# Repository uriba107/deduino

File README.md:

# DEDUino
Arduino Based DED for Falcon BMS.
Project Blog: http://pit.uriba.org

## Requirements:
### Hardware:
1. an Arduino or compatible board:
  * Arduino Uno (or compatible)
  * Arduino Micro (or compatible)
  * Arduino Due (or compatible)
  * all similar Arduino/Arduino-like variations (Mega/leonardo/pro Micro) will require code to be adjusted
2. For DED/PFL: One 2.8" or 3.2" 256*64 OLED display (yellow or green), SSD1322 based
  * [BuyDisplay 2.8" yellow on black oled](http://www.buydisplay.com/default/spi-2-8-inch-oled-arduino-256x64-graphic-module-with-pcb-yellow-on-black)
  * [BuyDisplay 3.2" green on black oled](http://www.buydisplay.com/default/spi-oled-manufacturer-256x64-display-panel-supplier-green-on-black)
  * other screens may be also compatible (as long as they are SSD1322 based) - but may require different wiring.
3. For FFI: one 1.3" 128*64 OLED white on black. SSD1306 or SH1106 based
  * [Adafruit 1.3" 128*64 OLED](http://www.adafruit.com/product/938)
  * Generic 1.3" OLED (off the internet), will do fine as long as it's of one of the supported chipsets.
  * Other displays might be also compatible - but may require code edit
4. For Indexers/Caution panel:
  * [PCF8574 8-bit I2C I/O Expander](http://www.ebay.com/sch/sis.html?_nkw=PCF8574P+PCF8574+DIP-16+NXP%2FPHI+Remote+8-bit+I%2FO+Expander+IC) - for Indexers
  * [MCP23017 16-bit I2C I/O Expander](http://www.ebay.com/sch/sis.html?_nkw=MCP23017-E%2FSP+DIP28+16-Bit+I%2FO+Expander+with+I2C+Interface+IC) - optional 16 bit extender (useful for caution panel and other things)
  * LEDs of your choosing (If using attached PCB design unmodified - 5mm pirahna leds are used)
  * Resistors (220-330 ohm reesistors would be a good place to start)
  * Legacy SPI lights are using [74HC595 Shift Register](http://www.adafruit.com/product/450) - you can find them on ebay as well.

### Software:
1. Arduino IDE
2. Windows Vista and up with .net 4.5 installed (XP does not support .net4.5 and I've not tested the supplied connector app with .net4.0)
3. Falcon BMS 4.32+

## How to use:
### Initial setup:
1. Download and install the Arduino IDE (if not already installed)
2. Download the Arduino code
3. In the Arduino IDE - "Add library" choose "U8g2_16bit" it's standard U8g2 2.12.6 with 16BIT support enabled (required for the large displays)
4. In "config.h" and uncomment the correct define for your arduino version (Uno, Micro or Due).
5. In "config.h" Uncomment the define statements for the periferials you want to use. please note that adding both DED and PFL may have an impact on performace.
6. Wire prereferials according the the pinout in the code. Please pay attention to the SCK and MOSI pins and the latchpins
7. Upload code to your Arduino.
8. Download the DEDuino Windows app and place it in a folder of your choosing (no installation required)

### running the project:
1. launch DEDuino App
2. Select proper COM port for the arduino to be used and hit "Start"
3. Once connected - Windows app will indicate connected status and all displays and leds should be blanked except for FFI screen that will show "00000".
4. Launch Falcon BMS - As soon as you enter the cockpit, all the instruments connected should display acording to the pit.

## Supported instruments:
1. Displays:
  * DED - Tier 1
  * FFI - Tier 1
  * PFD - Tier 1 (disabled by default due to performance considuration)
2. Lights:
  * Indexers - Tier 1
  * Caution Panel - Tier 1 (Disabled by default due to performance consideration)
3. Future supported instruments:
  * Glareshield lighs - TBD
  * Threat Warning Prime - TBD
  * CMDS - via OLED screen, TBD

## Knows issues:
1. Activating more the one large res display (DED/PFD) will cause performace degradation. Activating more then two might cause noticable lag without further optimization to Arduino code (not yet implemented).
2. "lamp test" might not work properly for Caution panel is some scenarios.
3. When using SPI for driving multiple light arrays, there are issues including freezes, wrongly timed blinks and all sort of wierd shananigans. That is way, I2C is now the primary, prefered protocol for driving lights. SPI support will not be extended, and only retained for comptability.

## PCB
In the PCB folder you would find Eagle files and PDFs with schematics and board drawings. These are the boards I'm working with. You can make them yourself by hand soldering the connectors (see schematics) or source them out to production. All boards were edited using the Free version of Eagle (version 7).

## Enclosures
In the "enclosure" folders you'll find some stractual stuff, like the foamboard DED box.

## Notes and remarks
While the project is OpenSource. Currently I'm holding back the source code for the PC connector application. That is done because The code is a mess, I need to properly document it before I release it. Hopfully sometime this year. Nothing secret about it, promise :)
Big Thanks to Oliver Kraus (olikraus) who wrote [u8glib](https://github.com/olikraus/u8glib)/[u8g2](https://github.com/olikraus/u8g2) without him, none of this would have been possible.

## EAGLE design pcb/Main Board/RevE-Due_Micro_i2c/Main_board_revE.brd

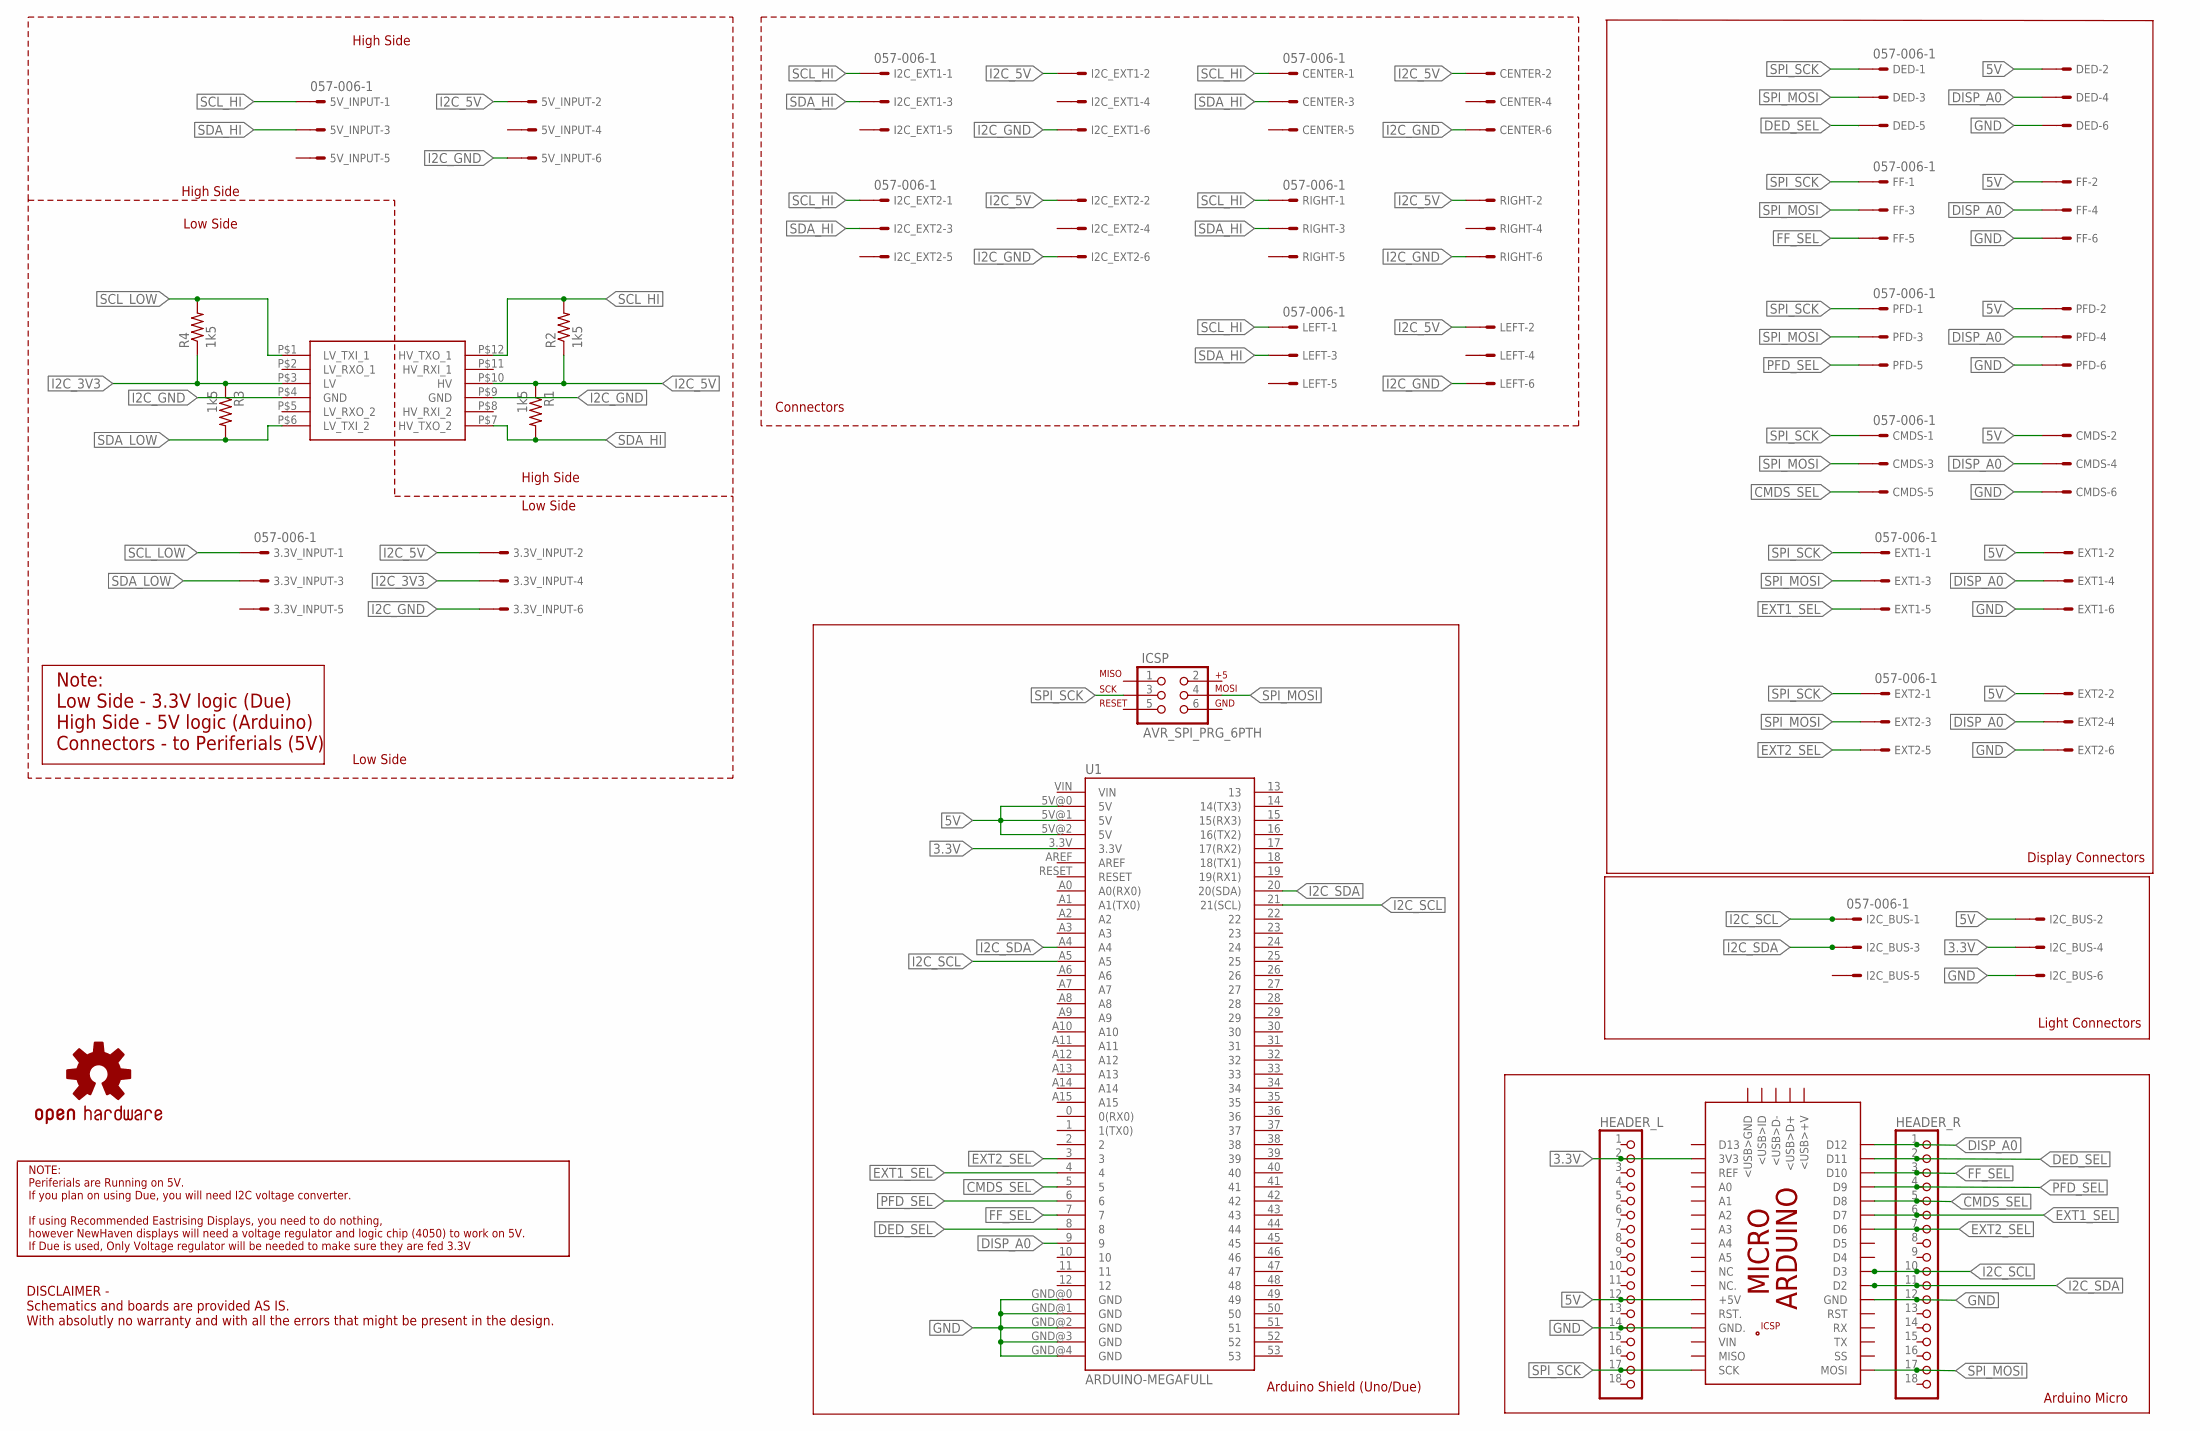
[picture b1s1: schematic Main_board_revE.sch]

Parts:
3.3V_INPUT, 5V_INPUT: 057-006-1
CENTER: 057-006-1
CMDS: 057-006-1
DED: 057-006-1
EXT1, EXT2: 057-006-1
FF: 057-006-1
HEADER_L: PINHD-1X18; 1X18
HEADER_R: PINHD-1X18; 1X18
I2C_BUS, I2C_EXT1, I2C_EXT2: 057-006-1
ICSP: AVR_SPI_PRG_6PTH; 2X3
LEFT: 057-006-1
LOGO1: OSHW-LOGOM; OSHW-LOGO-M
PFD: 057-006-1
R1, R2, R3, R4: 1k5; 0805
RIGHT: 057-006-1
U1: ARDUINO-MEGAFULL; ARDUINO_MEGA
U$1: LOGIC_LEVEL_CONVERTER

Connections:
3.3V: HEADER_L.2, I2C_BUS.4, U1.3.3V
5V: CMDS.2, DED.2, EXT1.2, EXT2.2, FF.2, HEADER_L.12, I2C_BUS.2, PFD.2, U1.5V@0 (5V), U1.5V@1 (5V), U1.5V@2 (5V)
CMDS_SEL: CMDS.5, HEADER_R.5, U1.5
DED_SEL: DED.5, HEADER_R.2, U1.8
DISP_A0: CMDS.4, DED.4, EXT1.4, EXT2.4, FF.4, HEADER_R.1, PFD.4, U1.9
EXT1_SEL: EXT1.5, HEADER_R.6, U1.4
EXT2_SEL: EXT2.5, HEADER_R.7, U1.3
FF_SEL: FF.5, HEADER_R.3, U1.7
GND: CMDS.6, DED.6, EXT1.6, EXT2.6, FF.6, HEADER_L.14, HEADER_R.12, I2C_BUS.6, PFD.6, U1.GND@0 (GND), U1.GND@1 (GND), U1.GND@2 (GND), U1.GND@3 (GND), U1.GND@4 (GND)
I2C_3V3: 3.3V_INPUT.4, R3.1, R4.1, U$1.P$3 (LV)
I2C_5V: 3.3V_INPUT.2, 5V_INPUT.2, CENTER.2, I2C_EXT1.2, I2C_EXT2.2, LEFT.2, R1.1, R2.1, RIGHT.2, U$1.P$10 (HV)
I2C_GND: 3.3V_INPUT.6, 5V_INPUT.6, CENTER.6, I2C_EXT1.6, I2C_EXT2.6, LEFT.6, RIGHT.6, U$1.P$4 (GND), U$1.P$9 (GND)
I2C_SCL: HEADER_R.10, I2C_BUS.1, U1.21 (21(SCL)), U1.A5
I2C_SDA: HEADER_R.11, I2C_BUS.3, U1.20 (20(SDA)), U1.A4
PFD_SEL: HEADER_R.4, PFD.5, U1.6
SCL_HI: 5V_INPUT.1, CENTER.1, I2C_EXT1.1, I2C_EXT2.1, LEFT.1, R2.2, RIGHT.1, U$1.P$12 (HV_TXO_1)
SCL_LOW: 3.3V_INPUT.1, R4.2, U$1.P$1 (LV_TXI_1)
SDA_HI: 5V_INPUT.3, CENTER.3, I2C_EXT1.3, I2C_EXT2.3, LEFT.3, R1.2, RIGHT.3, U$1.P$7 (HV_TXO_2)
SDA_LOW: 3.3V_INPUT.3, R3.2, U$1.P$6 (LV_TXI_2)
SPI_MOSI: CMDS.3, DED.3, EXT1.3, EXT2.3, FF.3, HEADER_R.17, ICSP.4, PFD.3
SPI_SCK: CMDS.1, DED.1, EXT1.1, EXT2.1, FF.1, HEADER_L.17, ICSP.3, PFD.1

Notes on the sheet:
Arduino Shield (Uno/Due)
Arduino Micro
Light Connectors
Display Connectors
DISCLAIMER - Schematics and boards are provided AS IS. With absolutly no warranty and with all the errors that might be present in the design.
NOTE: Periferials are Running on 5V. If you plan on using Due, you will need I2C voltage converter. If using Recommended Eastrising Displays, you need to do nothing, however NewHaven displays will need a voltage regulator and logic chip (4050) to work on 5V. If Due is used, Only Voltage regulator w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
Low Side
High Side
Connectors
Note: Low Side - 3.3V logic (Due) High Side - 5V logic (Arduino) Connectors - to Periferials (5V)

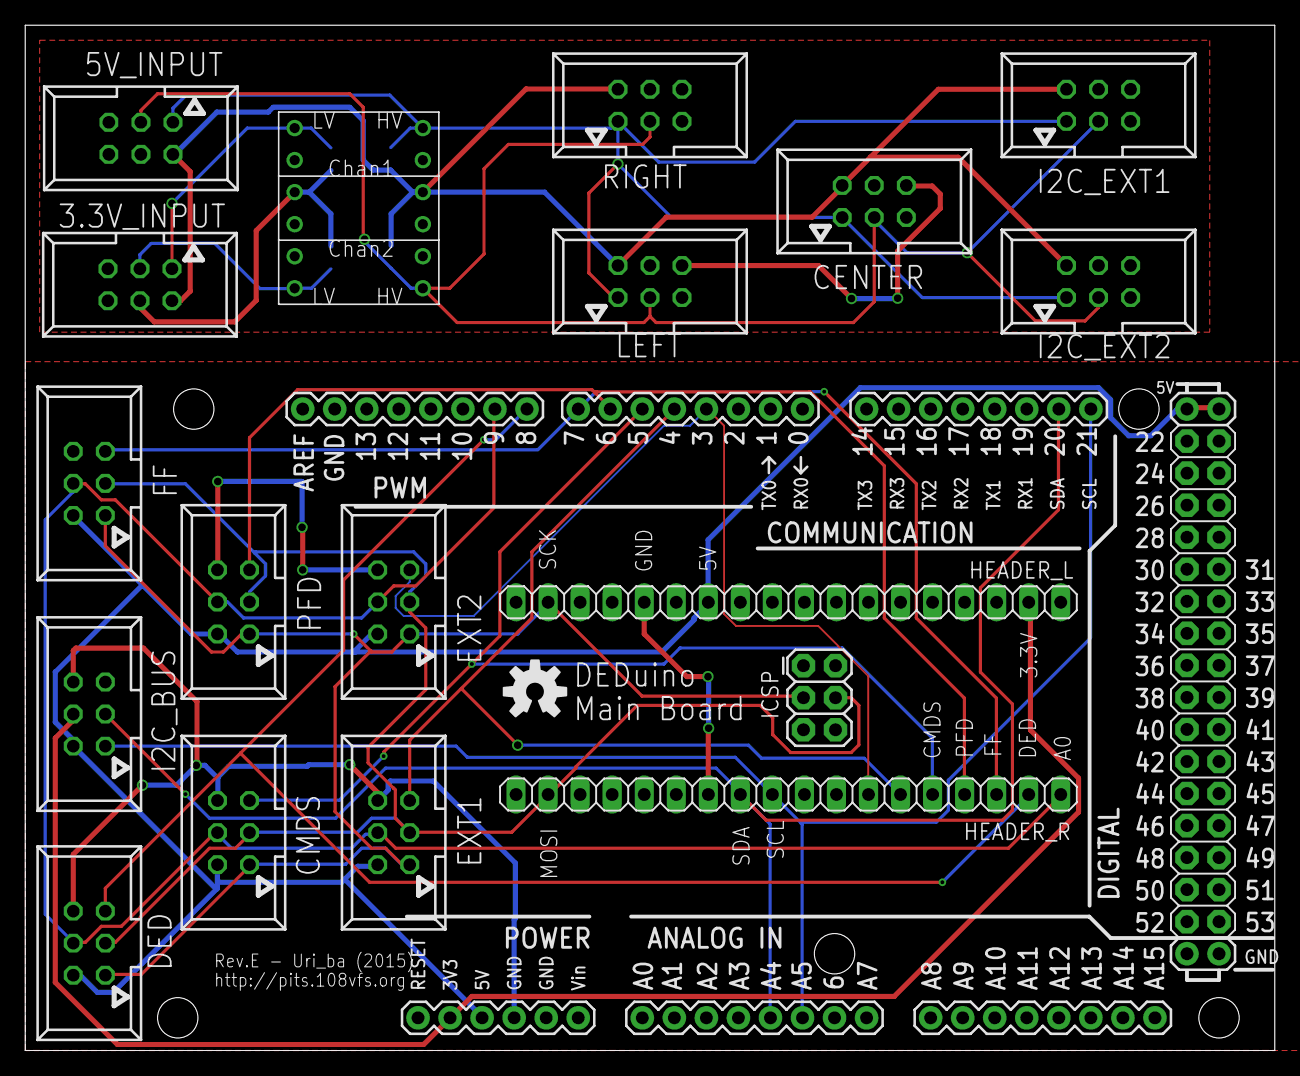
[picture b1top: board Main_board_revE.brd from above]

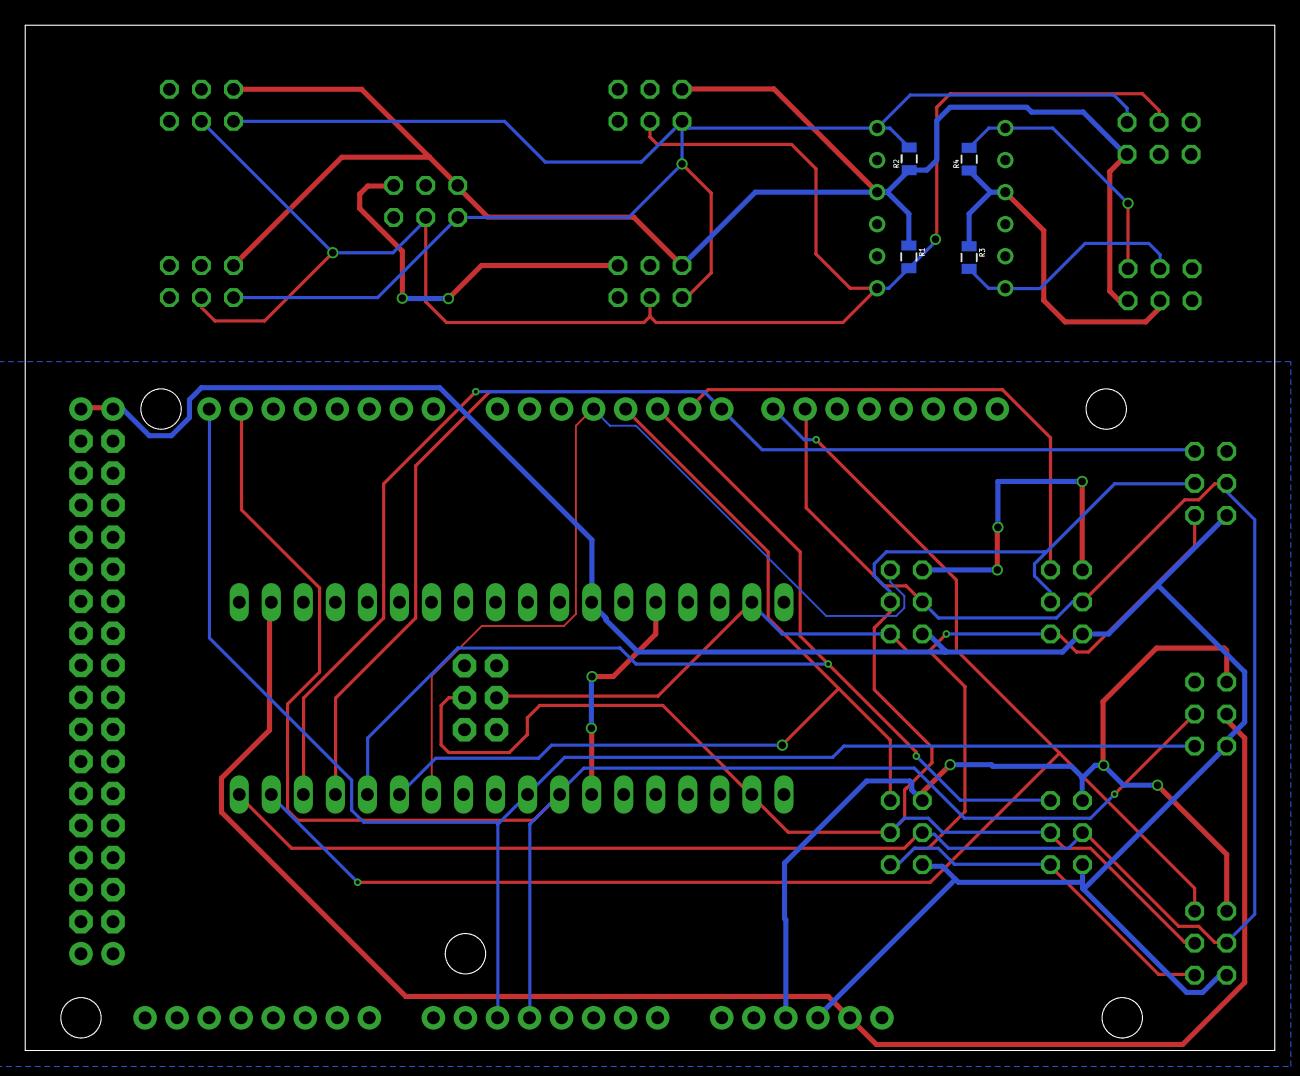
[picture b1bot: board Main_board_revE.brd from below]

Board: 2 copper layers, 99.1 x 81.3 mm, 24 parts (4 on the bottom side), 21 nets.

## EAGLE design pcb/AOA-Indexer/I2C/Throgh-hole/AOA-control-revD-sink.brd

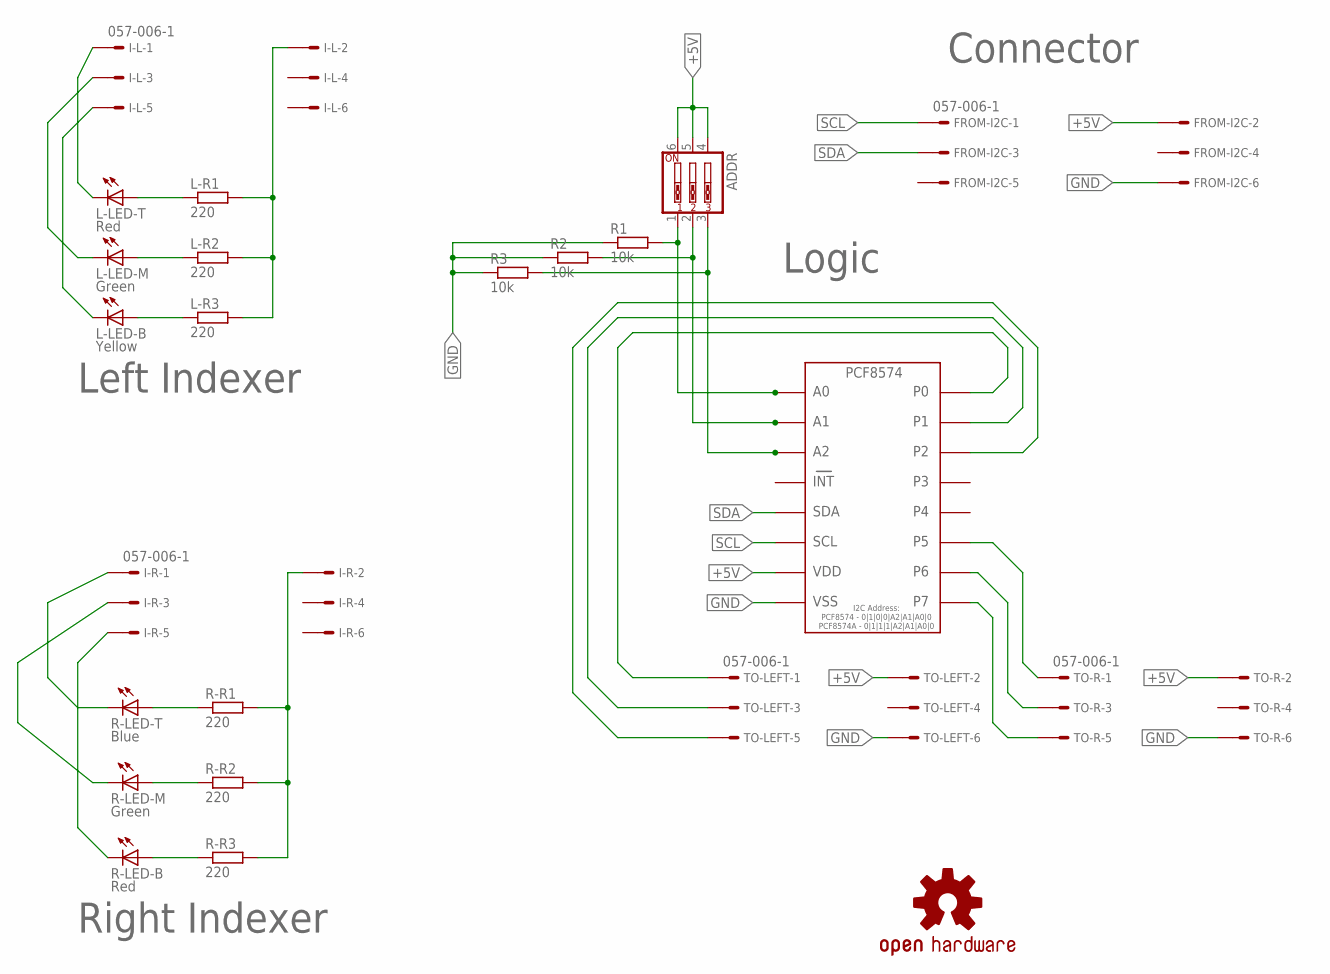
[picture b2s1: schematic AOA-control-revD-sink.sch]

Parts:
ADDR: SW_DIP-3; EDG-03
FROM-I2C: 057-006-1
I-L: 057-006-1
I-R: 057-006-1
L-LED-B: Yellow; CP41B
L-LED-M: Green; CP41B
L-LED-T: Red; CP41B
L-R1, L-R2, L-R3: 220; 0204/7
LOGO1: OSHW-LOGOS; OSHW-LOGO-S
R1, R2, R3: 10k; 0204/7
R-LED-B: Red; CP41B
R-LED-M: Green; CP41B
R-LED-T: Blue; CP41B
R-R1, R-R2, R-R3: 220; 0204/7
TO-LEFT: 057-006-1
TO-R: 057-006-1
U$1: PCF8574P/AP; DIP16

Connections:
5V-L: I-L.2, L-R1.2, L-R2.2, L-R3.2
5V-R: I-R.2, R-R1.2, R-R2.2, R-R3.2
+5V: ADDR.4, ADDR.5, ADDR.6, FROM-I2C.2, TO-LEFT.2, TO-R.2, U$1.VDD
A0: ADDR.1, R1.2, U$1.A0
A1: ADDR.2, R2.2, U$1.A1
A2: ADDR.3, R3.2, U$1.A2
GND: FROM-I2C.6, R1.1, R2.1, R3.1, TO-LEFT.6, TO-R.6, U$1.VSS
unnamed: I-L.1, L-LED-T.1 (C), L-LED-T.4 (C)
unnamed: I-L.3, L-LED-M.1 (C), L-LED-M.4 (C)
unnamed: I-L.5, L-LED-B.1 (C), L-LED-B.4 (C)
unnamed: R-LED-B.2 (A), R-LED-B.3 (A), R-R3.1
unnamed: I-R.1, R-LED-T.1 (C), R-LED-T.4 (C)
unnamed: I-R.3, R-LED-M.1 (C), R-LED-M.4 (C)
unnamed: I-R.5, R-LED-B.1 (C), R-LED-B.4 (C)
unnamed: R-LED-M.2 (A), R-LED-M.3 (A), R-R2.1
unnamed: R-LED-T.2 (A), R-LED-T.3 (A), R-R1.1
unnamed: L-LED-T.2 (A), L-LED-T.3 (A), L-R1.1
unnamed: TO-LEFT.1, U$1.P0
unnamed: L-LED-M.2 (A), L-LED-M.3 (A), L-R2.1
unnamed: L-LED-B.2 (A), L-LED-B.3 (A), L-R3.1
unnamed: TO-LEFT.3, U$1.P1
unnamed: TO-LEFT.5, U$1.P2
unnamed: TO-R.1, U$1.P5
unnamed: TO-R.3, U$1.P6
unnamed: TO-R.5, U$1.P7
SCL: FROM-I2C.1, U$1.SCL
SDA: FROM-I2C.3, U$1.SDA

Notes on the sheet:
Connector
Logic
Left Indexer
Right Indexer

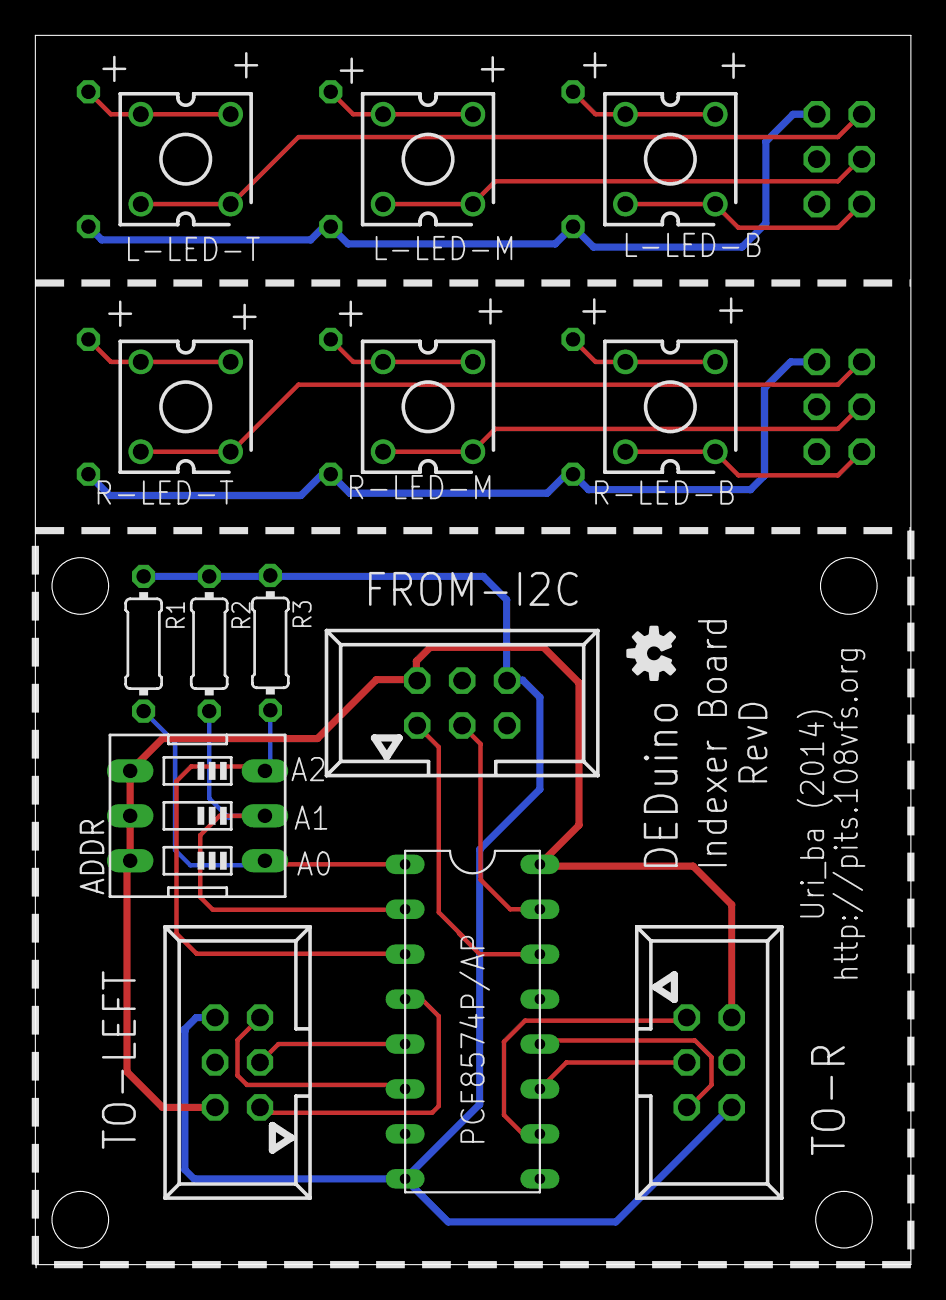
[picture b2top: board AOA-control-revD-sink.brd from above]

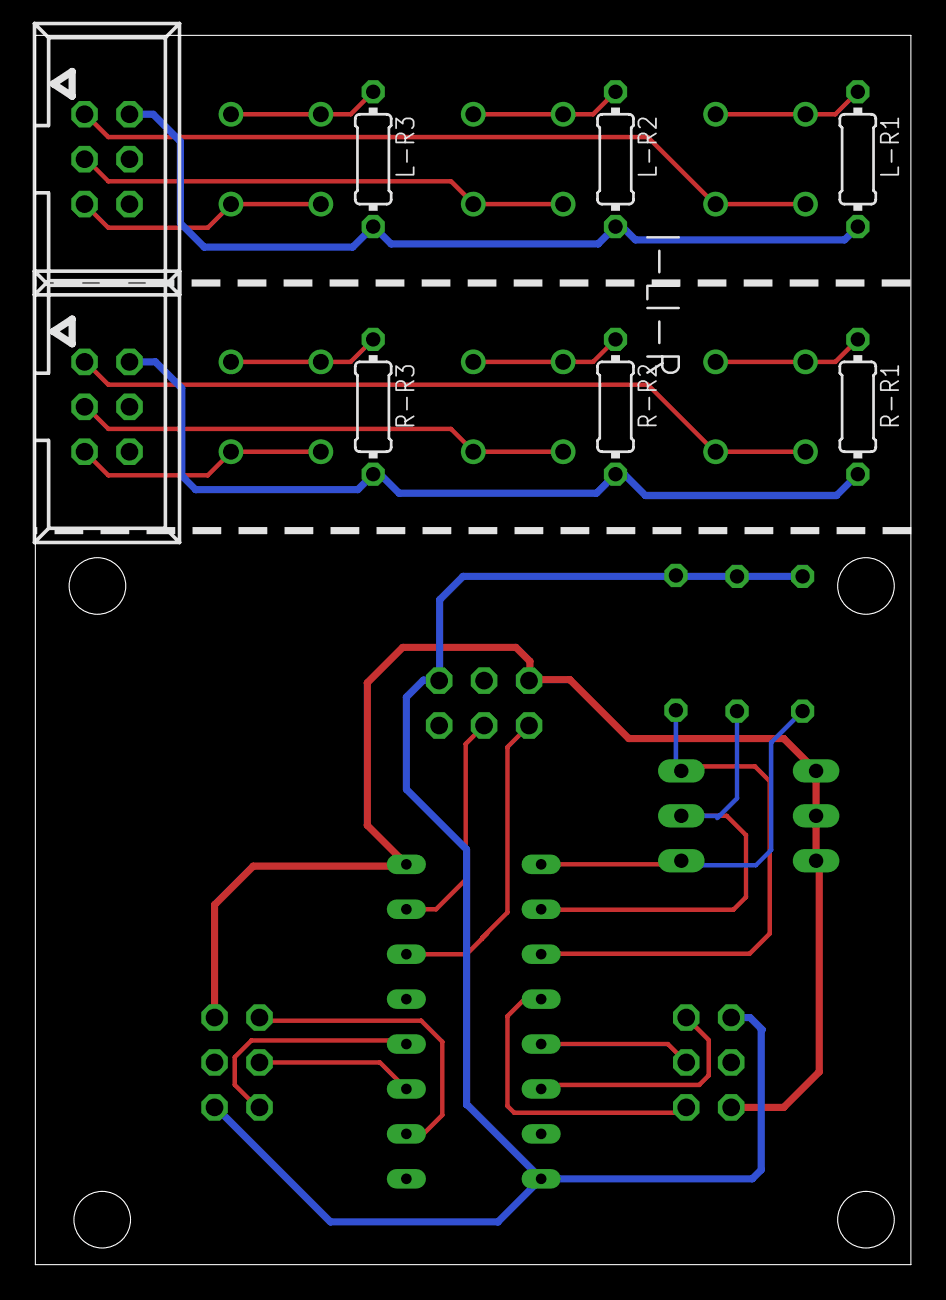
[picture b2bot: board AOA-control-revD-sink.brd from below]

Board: 2 copper layers, 49.5 x 69.5 mm, 23 parts (8 on the bottom side), 27 nets.

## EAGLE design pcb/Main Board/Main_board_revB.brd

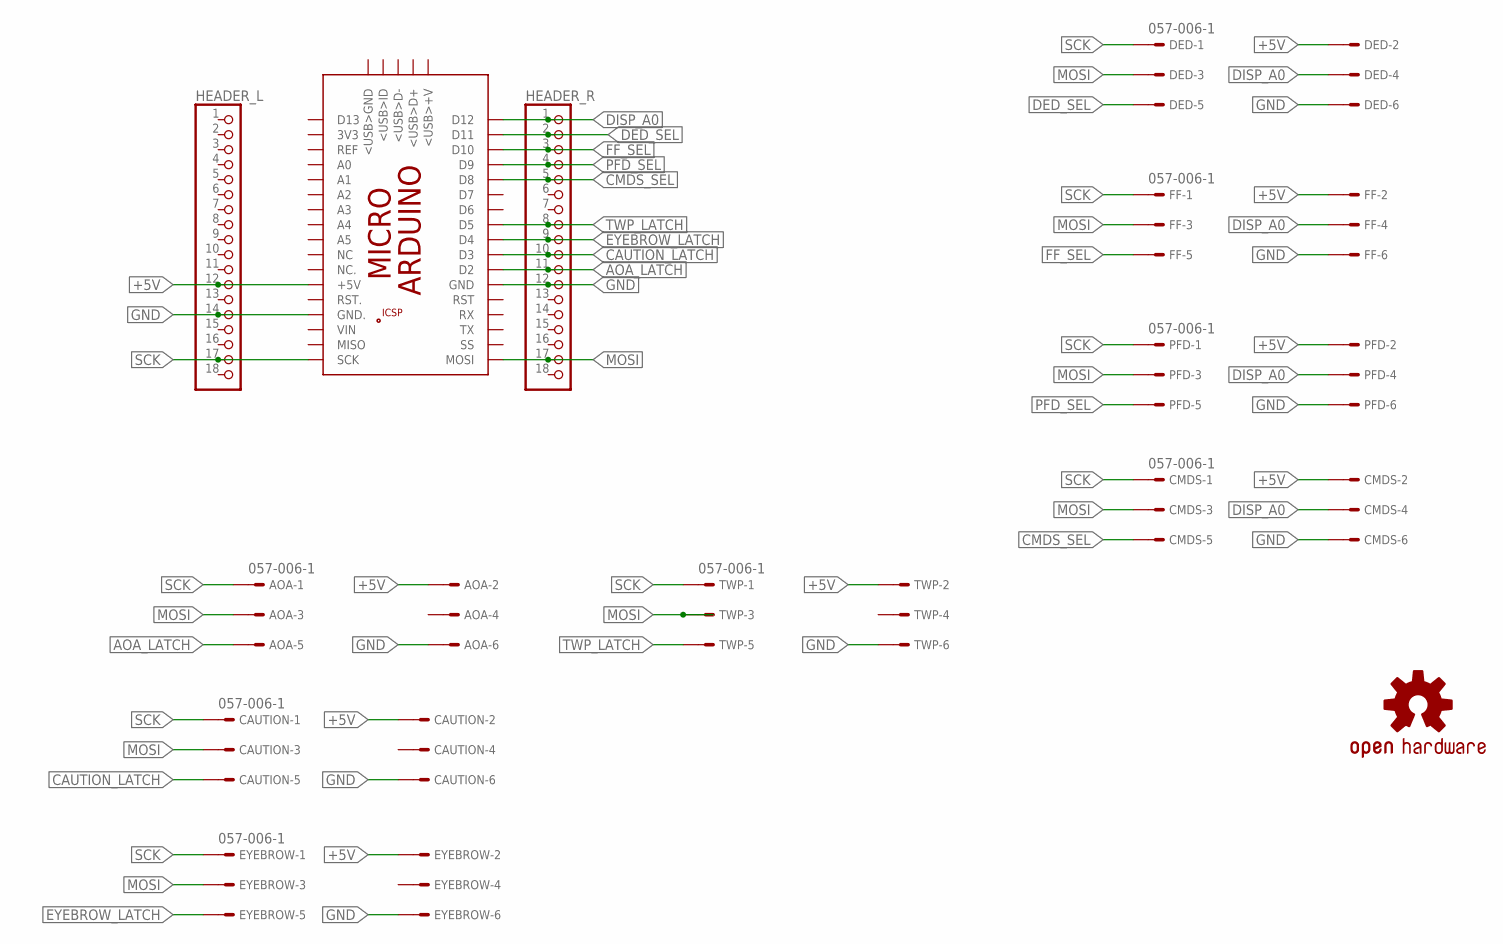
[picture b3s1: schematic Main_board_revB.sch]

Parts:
AOA: 057-006-1
CAUTION: 057-006-1
CMDS: 057-006-1
DED: 057-006-1
EYEBROW: 057-006-1
FF: 057-006-1
HEADER_L: PINHD-1X18; 1X18
HEADER_R: PINHD-1X18; 1X18
LOGO1: OSHW-LOGOL; OSHW-LOGO-L
PFD: 057-006-1
TWP: 057-006-1

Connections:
+5V: AOA.2, CAUTION.2, CMDS.2, DED.2, EYEBROW.2, FF.2, HEADER_L.12, PFD.2, TWP.2
AOA_LATCH: AOA.5, HEADER_R.11
CAUTION_LATCH: CAUTION.5, HEADER_R.10
CMDS_SEL: CMDS.5, HEADER_R.5
DED_SEL: DED.5, HEADER_R.2
DISP_A0: CMDS.4, DED.4, FF.4, HEADER_R.1, PFD.4
EYEBROW_LATCH: EYEBROW.5, HEADER_R.9
FF_SEL: FF.5, HEADER_R.3
GND: AOA.6, CAUTION.6, CMDS.6, DED.6, EYEBROW.6, FF.6, HEADER_L.14, HEADER_R.12, PFD.6, TWP.6
MOSI: AOA.3, CAUTION.3, CMDS.3, DED.3, EYEBROW.3, FF.3, HEADER_R.17, PFD.3, TWP.3
PFD_SEL: HEADER_R.4, PFD.5
SCK: AOA.1, CAUTION.1, CMDS.1, DED.1, EYEBROW.1, FF.1, HEADER_L.17, PFD.1, TWP.1
TWP_LATCH: HEADER_R.8, TWP.5

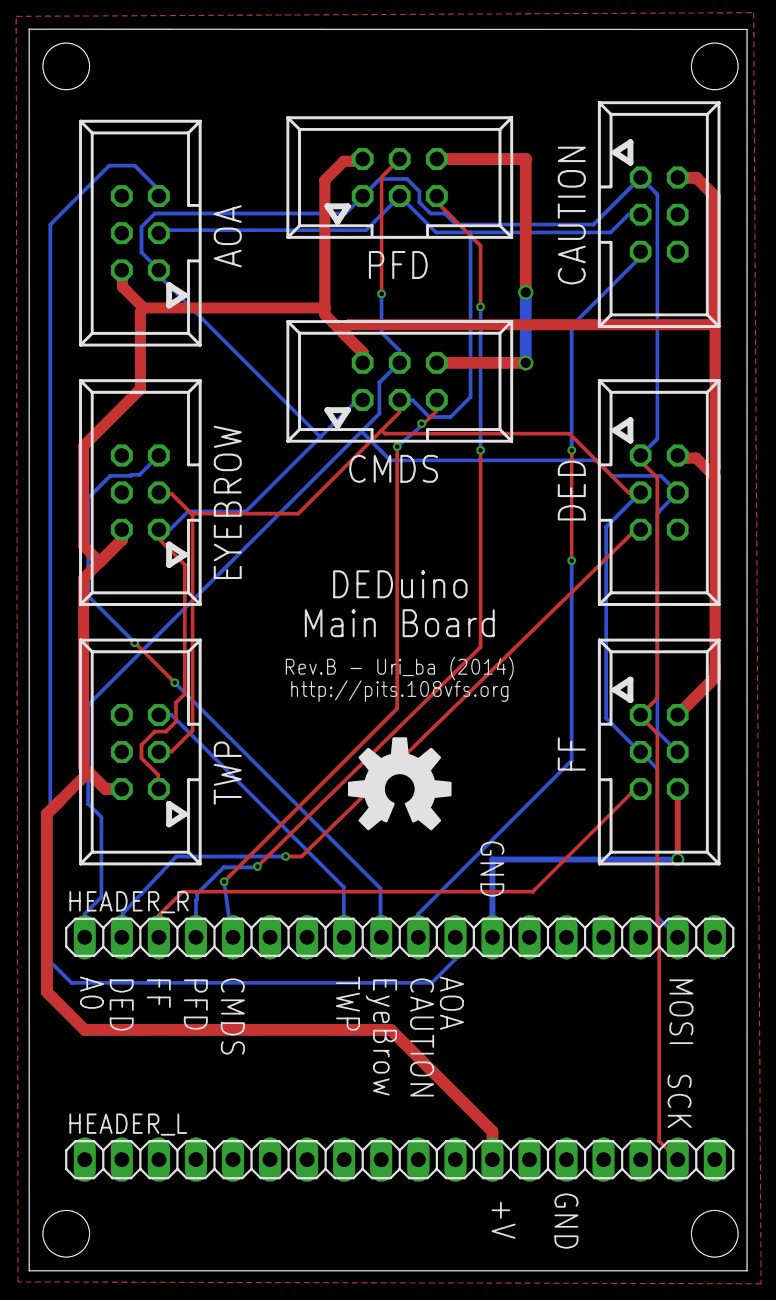
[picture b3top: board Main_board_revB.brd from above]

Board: 2 copper layers, 49.2 x 85.1 mm, 11 parts (0 on the bottom side), 13 nets.

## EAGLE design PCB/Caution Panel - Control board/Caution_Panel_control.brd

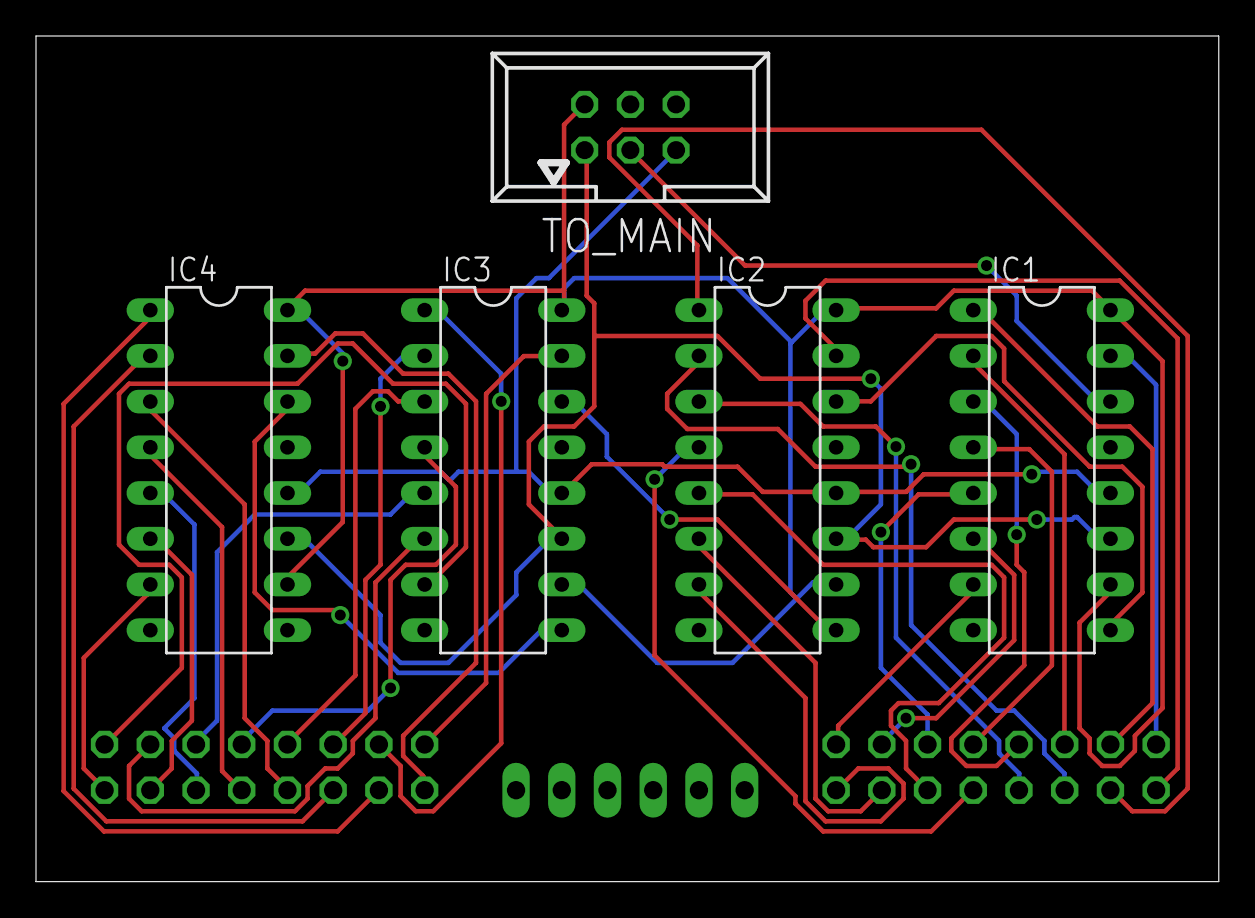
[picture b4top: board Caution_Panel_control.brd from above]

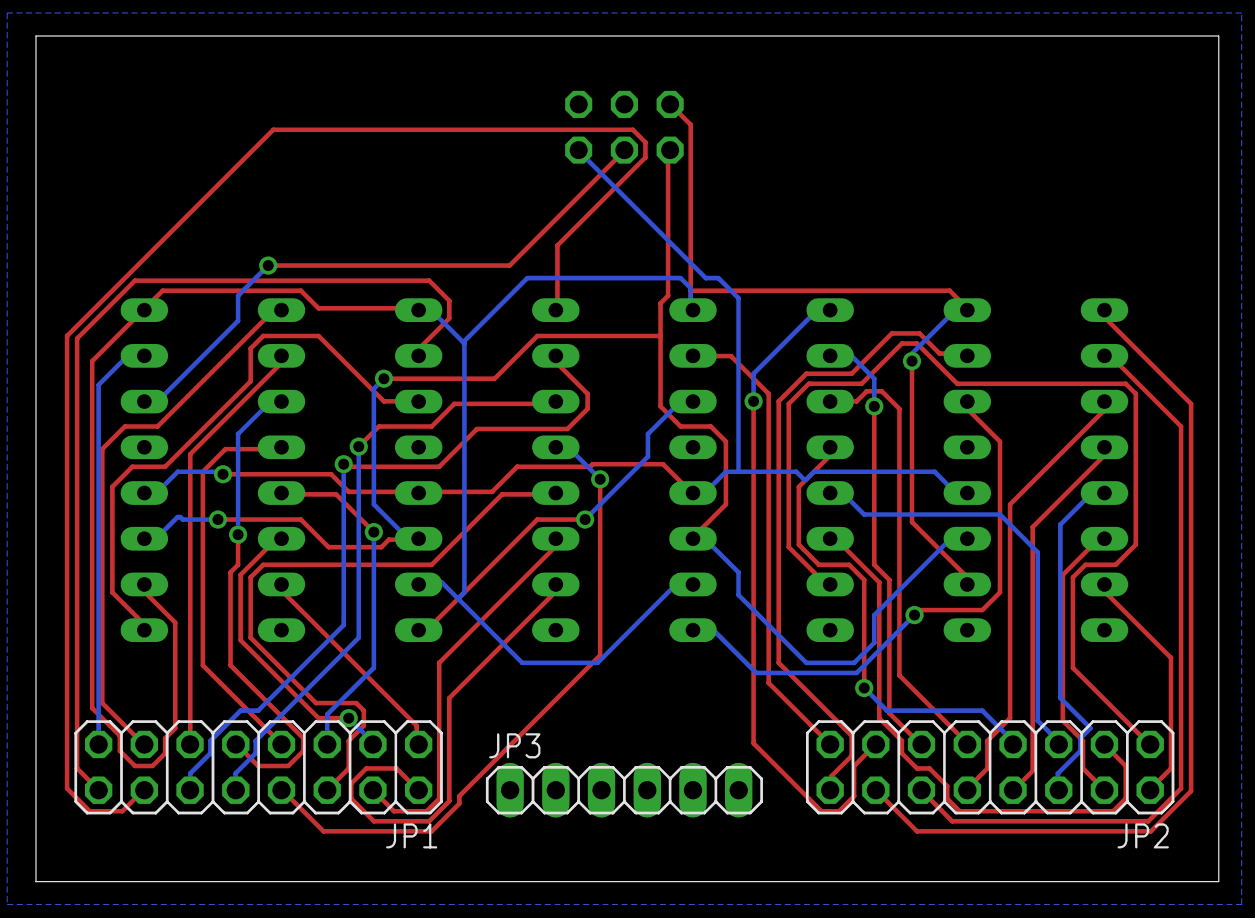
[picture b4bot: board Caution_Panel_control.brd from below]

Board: 2 copper layers, 65.7 x 47.0 mm, 8 parts (3 on the bottom side), 40 nets.

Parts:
IC1, IC2, IC3, IC4: 74HC595N; DIL16
JP1, JP2: 2X08
JP3: 1X06
TO_MAIN: 057-006-1

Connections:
+5V: IC1.10, IC1.16, IC2.10, IC2.16, IC3.10, IC3.16, IC4.10, IC4.16, TO_MAIN.2
CAUTION_LATCH: IC1.12, IC2.12, IC3.12, IC4.12, TO_MAIN.5
DATA_IC2: IC1.9, IC2.14
DATA_IC3: IC2.9, IC3.14
DATA_IC4: IC3.9, IC4.14
GND: IC1.8, IC1.13, IC2.8, IC2.13, IC3.8, IC3.13, IC4.8, IC4.13, JP3.1, JP3.2, JP3.3, JP3.4, JP3.5, JP3.6, TO_MAIN.6
LIGHT_CLK: IC1.11, IC2.11, IC3.11, IC4.11, TO_MAIN.1
LIGHT_DATA: IC1.14, TO_MAIN.3
unnamed: IC1.15, JP1.15
unnamed: IC1.1, JP1.13
unnamed: IC1.2, JP1.11
unnamed: IC1.3, JP1.9
unnamed: IC1.4, JP1.7
unnamed: IC1.5, JP1.5
unnamed: IC1.6, JP1.3
unnamed: IC1.7, JP1.1
unnamed: IC2.15, JP1.16
unnamed: IC2.1, JP1.14
unnamed: IC2.2, JP1.12
unnamed: IC2.3, JP1.10
unnamed: IC2.4, JP1.8
unnamed: IC2.5, JP1.6
unnamed: IC2.6, JP1.4
unnamed: IC2.7, JP1.2
unnamed: IC4.7, JP2.2
unnamed: IC4.6, JP2.4
unnamed: IC4.5, JP2.6
unnamed: IC4.4, JP2.8
unnamed: IC4.3, JP2.10
unnamed: IC4.2, JP2.12
unnamed: IC4.1, JP2.14
unnamed: IC4.15, JP2.16
unnamed: IC3.7, JP2.1
unnamed: IC3.5, JP2.5
unnamed: IC3.6, JP2.3
unnamed: IC3.4, JP2.7
unnamed: IC3.3, JP2.9
unnamed: IC3.2, JP2.11
unnamed: IC3.1, JP2.13
unnamed: IC3.15, JP2.15

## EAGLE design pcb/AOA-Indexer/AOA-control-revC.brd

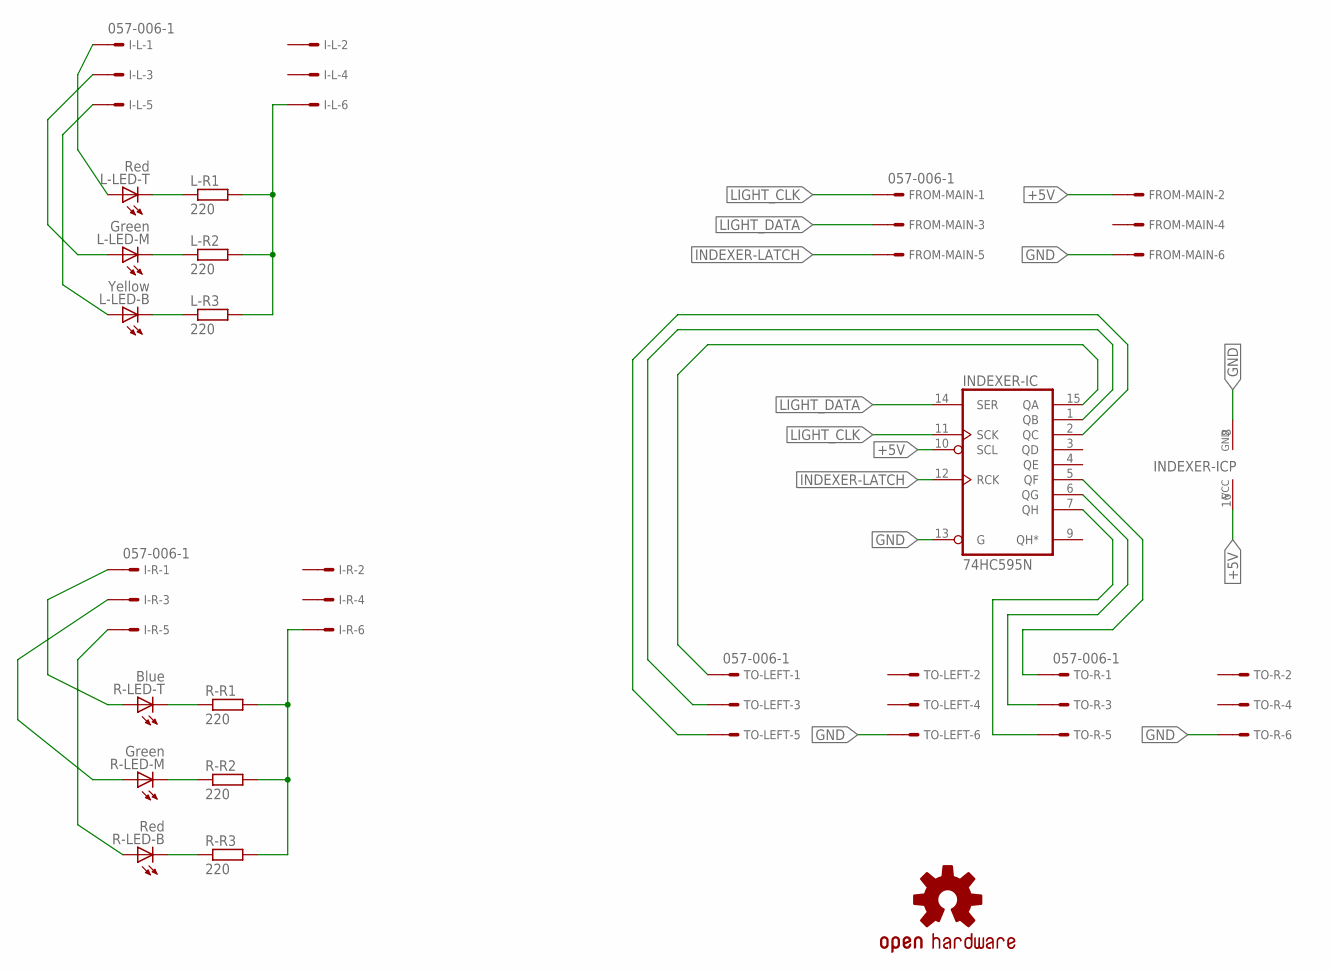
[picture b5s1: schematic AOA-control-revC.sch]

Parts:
FROM-MAIN: 057-006-1
I-L: 057-006-1
I-R: 057-006-1
INDEXER-IC: 74HC595N; DIL16
L-LED-B: Yellow; CP41B
L-LED-M: Green; CP41B
L-LED-T: Red; CP41B
L-R1, L-R2, L-R3: 220; 0204/7
LOGO1: OSHW-LOGOS; OSHW-LOGO-S
R-LED-B: Red; CP41B
R-LED-M: Green; CP41B
R-LED-T: Blue; CP41B
R-R1, R-R2, R-R3: 220; 0204/7
TO-LEFT: 057-006-1
TO-R: 057-006-1

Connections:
+5V: FROM-MAIN.2, INDEXER-IC.10 (SCL), INDEXER-IC.16 (VCC)
GND: FROM-MAIN.6, I-L.6, I-R.6, INDEXER-IC.8 (GND), INDEXER-IC.13 (G), L-R1.2, L-R2.2, L-R3.2, R-R1.2, R-R2.2, R-R3.2, TO-LEFT.6, TO-R.6
INDEXER-LATCH: FROM-MAIN.5, INDEXER-IC.12 (RCK)
L-B: INDEXER-IC.2 (QC), TO-LEFT.5
L-M: INDEXER-IC.1 (QB), TO-LEFT.3
L-T: INDEXER-IC.15 (QA), TO-LEFT.1
LIGHT_CLK: FROM-MAIN.1, INDEXER-IC.11 (SCK)
LIGHT_DATA: FROM-MAIN.3, INDEXER-IC.14 (SER)
unnamed: I-L.1, L-LED-T.2 (A), L-LED-T.3 (A)
unnamed: I-L.3, L-LED-M.2 (A), L-LED-M.3 (A)
unnamed: I-L.5, L-LED-B.2 (A), L-LED-B.3 (A)
unnamed: R-LED-B.1 (C), R-LED-B.4 (C), R-R3.1
unnamed: I-R.1, R-LED-T.2 (A), R-LED-T.3 (A)
unnamed: I-R.3, R-LED-M.2 (A), R-LED-M.3 (A)
unnamed: I-R.5, R-LED-B.2 (A), R-LED-B.3 (A)
unnamed: L-LED-B.1 (C), L-LED-B.4 (C), L-R3.1
unnamed: L-LED-M.1 (C), L-LED-M.4 (C), L-R2.1
unnamed: L-LED-T.1 (C), L-LED-T.4 (C), L-R1.1
unnamed: R-LED-M.1 (C), R-LED-M.4 (C), R-R2.1
unnamed: R-LED-T.1 (C), R-LED-T.4 (C), R-R1.1
R-B: INDEXER-IC.7 (QH), TO-R.5
R-M: INDEXER-IC.6 (QG), TO-R.3
R-T: INDEXER-IC.5 (QF), TO-R.1

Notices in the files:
parts and their libraries:
SparkFun-Aesthetics: Licensing: Creative Commons ShareAlike 4.0 International - https://creativecommons.org/licenses/by-sa/4.0
SparkFun-Boards: Licensing: CC v3.0 Share-Alike You are welcome to use this library for commercial purposes.
